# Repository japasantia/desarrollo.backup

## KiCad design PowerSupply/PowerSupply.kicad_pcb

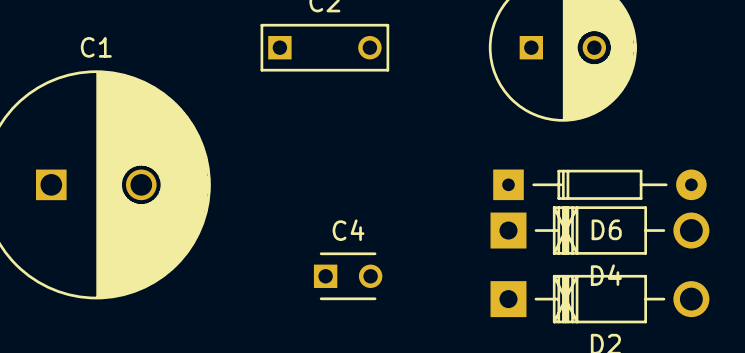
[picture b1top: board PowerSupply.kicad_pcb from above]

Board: 2 copper layers, 7 parts (0 on the bottom side), 3 nets, no tracks yet.

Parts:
C1: 3300uF; C_Radial_D12.5_L25_P5
C2: 470nF; C_Rect_L7_W2.5_P5
C4: 100nF; C_Disc_D3_P2.5
C6: 1uF; C_Radial_D8_L11.5_P3.5
D2: 1N4007; Diode_DO-41_SOD81_Horizontal_RM10
D4: D1N4001; Diode_DO-41_SOD81_Horizontal_RM10
D6: D; Diode_DO-35_SOD27_Horizontal_RM10

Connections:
/VDC_IN: C1.1, C2.1, D2.1
/VDC_OUT: C6.1, D4.1, D6.2
GND: C1.2, C2.2, C4.2, C6.2

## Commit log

2018-01-07 Commit inicial. Respaldo de desarrollo
    - Se elimina el repositorio anterior
    - Unicamente como medio de respaldo
2018-01-15 Respaldo
2018-01-18 Respaldo + archivos eliminados
    - Se eliminan archivos de CenditLab -> fusion de modulos
    - Modulos antiguos se descartan
2018-01-29 Respaldo de desarrollo
2018-02-12 Respaldo
    - Proyectos PIC
    - Se recompilan proyectos CDC USB
    - App bootloader HID reconstruido en Linux
